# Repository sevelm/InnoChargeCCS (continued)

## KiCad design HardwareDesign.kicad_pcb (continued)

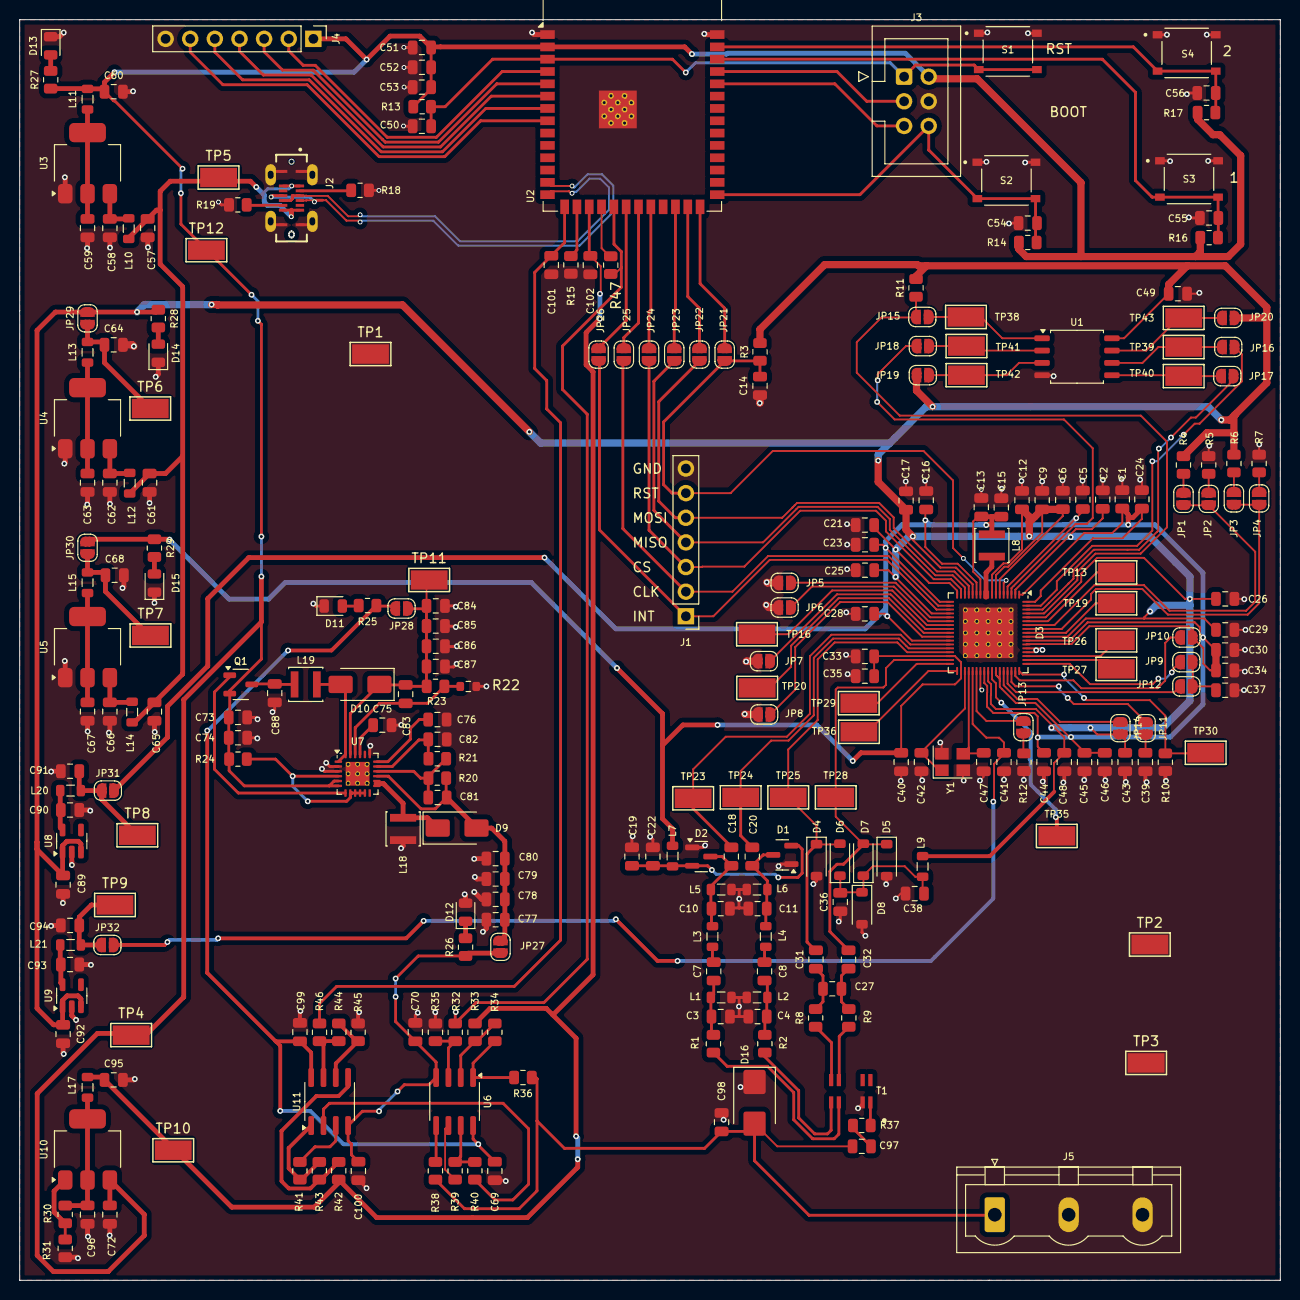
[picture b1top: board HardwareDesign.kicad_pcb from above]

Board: 2 copper layers, 130.0 x 130.0 mm, 271 parts (0 on the bottom side), 147 nets.

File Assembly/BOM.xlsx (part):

Designator | Value | Footprint | JLCPCB Part No# | Qty
L9 | GZ2012D601TF | Inductor_SMD:L_0805_2012Metric | C1017 | 1
L10 | GZ2012D601TF | Inductor_SMD:L_0805_2012Metric | C1017 | 1
L11 | GZ2012D601TF | Inductor_SMD:L_0805_2012Metric | C1017 | 1
L12 | GZ2012D601TF | Inductor_SMD:L_0805_2012Metric | C1017 | 1
L13 | GZ2012D601TF | Inductor_SMD:L_0805_2012Metric | C1017 | 1
L14 | GZ2012D601TF | Inductor_SMD:L_0805_2012Metric | C1017 | 1
L15 | GZ2012D601TF | Inductor_SMD:L_0805_2012Metric | C1017 | 1
L17 | GZ2012D601TF | Inductor_SMD:L_0805_2012Metric | C1017 | 1
L20 | GZ2012D601TF | Inductor_SMD:L_0805_2012Metric | C1017 | 1
L21 | GZ2012D601TF | Inductor_SMD:L_0805_2012Metric | C1017 | 1
C75 | 10nF | Capacitor_SMD:C_0805_2012Metric | C1710 | 1
C76 | 4.7nF | Capacitor_SMD:C_0805_2012Metric | C1744 | 1
C77 | 4.7uF | Capacitor_SMD:C_0805_2012Metric | C1779 | 1
C78 | 4.7uF | Capacitor_SMD:C_0805_2012Metric | C1779 | 1
C79 | 4.7uF | Capacitor_SMD:C_0805_2012Metric | C1779 | 1
C80 | 4.7uF | Capacitor_SMD:C_0805_2012Metric | C1779 | 1
C84 | 4.7uF | Capacitor_SMD:C_0805_2012Metric | C1779 | 1
C85 | 4.7uF | Capacitor_SMD:C_0805_2012Metric | C1779 | 1
C86 | 4.7uF | Capacitor_SMD:C_0805_2012Metric | C1779 | 1
C87 | 4.7uF | Capacitor_SMD:C_0805_2012Metric | C1779 | 1
C88 | 4.7uF | Capacitor_SMD:C_0805_2012Metric | C1779 | 1
C42 | 12pF | Capacitor_SMD:C_0805_2012Metric | C1792 | 1
C47 | 12pF | Capacitor_SMD:C_0805_2012Metric | C1792 | 1
C98 | 330pF | Capacitor_SMD:C_0805_2012Metric | C1815 | 1
C83 | 6.8pF | Capacitor_SMD:C_0805_2012Metric | C1832 | 1
D11 | LED | LED_SMD:LED_0805_2012Metric | C2297 | 1
D12 | LED | LED_SMD:LED_0805_2012Metric | C2297 | 1
D13 | LED | LED_SMD:LED_0805_2012Metric | C2297 | 1
D14 | LED | LED_SMD:LED_0805_2012Metric | C2297 | 1
D15 | LED | LED_SMD:LED_0805_2012Metric | C2297 | 1
C82 | 220nF | Capacitor_SMD:C_0805_2012Metric | C5378 | 1
U3 | AMS1117-3.3 | Package_TO_SOT_SMD:SOT-223-3_TabPin2 | C6186 | 1
U4 | AMS1117-3.3 | Package_TO_SOT_SMD:SOT-223-3_TabPin2 | C6186 | 1
U5 | AMS1117-3.3 | Package_TO_SOT_SMD:SOT-223-3_TabPin2 | C6186 | 1
D4 | B5819W SL | Diode_SMD:D_SOD-123 | C8598 | 1
D5 | B5819W SL | Diode_SMD:D_SOD-123 | C8598 | 1
D6 | B5819W SL | Diode_SMD:D_SOD-123 | C8598 | 1
D7 | B5819W SL | Diode_SMD:D_SOD-123 | C8598 | 1
Y1 | 25MHz X322525MOB4SI | Crystal:Crystal_SMD_3225-4Pin_3.2x2.5mm | C9006 | 1
C52 | 47uF | Capacitor_SMD:C_0805_2012Metric | C16780 | 1
C53 | 47uF | Capacitor_SMD:C_0805_2012Metric | C16780 | 1
C57 | 47uF | Capacitor_SMD:C_0805_2012Metric | C16780 | 1
C58 | 47uF | Capacitor_SMD:C_0805_2012Metric | C16780 | 1
C59 | 47uF | Capacitor_SMD:C_0805_2012Metric | C16780 | 1
C60 | 47uF | Capacitor_SMD:C_0805_2012Metric | C16780 | 1
C61 | 47uF | Capacitor_SMD:C_0805_2012Metric | C16780 | 1
C62 | 47uF | Capacitor_SMD:C_0805_2012Metric | C16780 | 1
C63 | 47uF | Capacitor_SMD:C_0805_2012Metric | C16780 | 1
C64 | 47uF | Capacitor_SMD:C_0805_2012Metric | C16780 | 1
C65 | 47uF | Capacitor_SMD:C_0805_2012Metric | C16780 | 1
C66 | 47uF | Capacitor_SMD:C_0805_2012Metric | C16780 | 1
C67 | 47uF | Capacitor_SMD:C_0805_2012Metric | C16780 | 1
C68 | 47uF | Capacitor_SMD:C_0805_2012Metric | C16780 | 1
C95 | 47uF | Capacitor_SMD:C_0805_2012Metric | C16780 | 1
R8 | 100Ω | Resistor_SMD:R_0805_2012Metric | C17408 | 1
R9 | 100Ω | Resistor_SMD:R_0805_2012Metric | C17408 | 1
R24 | 100Ω | Resistor_SMD:R_0805_2012Metric | C17408 | 1
R21 | 105KΩ | Resistor_SMD:R_0805_2012Metric | C17410 | 1
R3 | 10KΩ | Resistor_SMD:R_0805_2012Metric | C17414 | 1
R11 | 10KΩ | Resistor_SMD:R_0805_2012Metric | C17414 | 1
R13 | 10KΩ | Resistor_SMD:R_0805_2012Metric | C17414 | 1
R14 | 10KΩ | Resistor_SMD:R_0805_2012Metric | C17414 | 1
R15 | 10K | Resistor_SMD:R_0805_2012Metric | C17414 | 1
R16 | 10KΩ | Resistor_SMD:R_0805_2012Metric | C17414 | 1
R17 | 10KΩ | Resistor_SMD:R_0805_2012Metric | C17414 | 1
R40 | 10KΩ | Resistor_SMD:R_0805_2012Metric | C17414 | 1
R25 | 15KΩ | Resistor_SMD:R_0805_2012Metric | C17475 | 1
R26 | 15KΩ | Resistor_SMD:R_0805_2012Metric | C17475 | 1
R27 | 1KΩ | Resistor_SMD:R_0805_2012Metric | C17513 | 1
R28 | 1KΩ | Resistor_SMD:R_0805_2012Metric | C17513 | 1
R29 | 1KΩ | Resistor_SMD:R_0805_2012Metric | C17513 | 1
R32 | 1KΩ | Resistor_SMD:R_0805_2012Metric | C17513 | 1
R33 | 1KΩ | Resistor_SMD:R_0805_2012Metric | C17513 | 1
R36 | 1KΩ | Resistor_SMD:R_0805_2012Metric | C17513 | 1
R38 | 1KΩ | Resistor_SMD:R_0805_2012Metric | C17513 | 1
R39 | 1KΩ | Resistor_SMD:R_0805_2012Metric | C17513 | 1
R41 | 1KΩ | Resistor_SMD:R_0805_2012Metric | C17513 | 1
R42 | 1KΩ | Resistor_SMD:R_0805_2012Metric | C17513 | 1
R43 | 1KΩ | Resistor_SMD:R_0805_2012Metric | C17513 | 1
R44 | 1KΩ | Resistor_SMD:R_0805_2012Metric | C17513 | 1
R45 | 1KΩ | Resistor_SMD:R_0805_2012Metric | C17513 | 1
R47 | 1KΩ | Resistor_SMD:R_0805_2012Metric | C17513 | 1
R1 | 22Ω | Resistor_SMD:R_0805_2012Metric | C17561 | 1
R2 | 22Ω | Resistor_SMD:R_0805_2012Metric | C17561 | 1
R12 | 6.2KΩ | Resistor_SMD:R_0805_2012Metric | C17767 | 1
R34 | 7.5KΩ | Resistor_SMD:R_0805_2012Metric | C17807 | 1
R35 | 7.5KΩ | Resistor_SMD:R_0805_2012Metric | C17807 | 1
L8 | 4.7uH | Inductor_SMD:L_Sunlord_SWPA3015S | C19398 | 1
L18 | 4.7uH | Inductor_SMD:L_Sunlord_SWPA3015S | C19398 | 1
L19 | 4.7uH | Inductor_SMD:L_Sunlord_SWPA3015S | C19398 | 1
R37 | 180Ω | Resistor_SMD:R_0805_2012Metric | C25270 | 1
R4 | 3.3KΩ | Resistor_SMD:R_0805_2012Metric | C26010 | 1
R5 | 3.3KΩ | Resistor_SMD:R_0805_2012Metric | C26010 | 1
R6 | 3.3KΩ | Resistor_SMD:R_0805_2012Metric | C26010 | 1
R7 | 3.3KΩ | Resistor_SMD:R_0805_2012Metric | C26010 | 1
R18 | 5.1KΩ | Resistor_SMD:R_0805_2012Metric | C27834 | 1
R19 | 5.1KΩ | Resistor_SMD:R_0805_2012Metric | C27834 | 1
C1 | 100nF | Capacitor_SMD:C_0805_2012Metric | C28233 | 1
C2 | 100nF | Capacitor_SMD:C_0805_2012Metric | C28233 | 1
C5 | 100nF | Capacitor_SMD:C_0805_2012Metric | C28233 | 1
C6 | 100nF | Capacitor_SMD:C_0805_2012Metric | C28233 | 1
C12 | 100nF | Capacitor_SMD:C_0805_2012Metric | C28233 | 1
C14 | 100nF | Capacitor_SMD:C_0805_2012Metric | C28233 | 1
C15 | 100nF | Capacitor_SMD:C_0805_2012Metric | C28233 | 1
C16 | 100nF | Capacitor_SMD:C_0805_2012Metric | C28233 | 1
C17 | 100nF | Capacitor_SMD:C_0805_2012Metric | C28233 | 1
C21 | 100nF | Capacitor_SMD:C_0805_2012Metric | C28233 | 1
C23 | 100nF | Capacitor_SMD:C_0805_2012Metric | C28233 | 1
C24 | 100nF | Capacitor_SMD:C_0805_2012Metric | C28233 | 1
C25 | 100nF | Capacitor_SMD:C_0805_2012Metric | C28233 | 1
C26 | 100nF | Capacitor_SMD:C_0805_2012Metric | C28233 | 1
C28 | 100nF | Capacitor_SMD:C_0805_2012Metric | C28233 | 1
C29 | 100nF | Capacitor_SMD:C_0805_2012Metric | C28233 | 1
C30 | 100nF | Capacitor_SMD:C_0805_2012Metric | C28233 | 1
C31 | 100nF | Capacitor_SMD:C_0805_2012Metric | C28233 | 1
C32 | 100nF | Capacitor_SMD:C_0805_2012Metric | C28233 | 1
C34 | 100nF | Capacitor_SMD:C_0805_2012Metric | C28233 | 1
C35 | 100nF | Capacitor_SMD:C_0805_2012Metric | C28233 | 1
C36 | 100nF | Capacitor_SMD:C_0805_2012Metric | C28233 | 1
C37 | 100nF | Capacitor_SMD:C_0805_2012Metric | C28233 | 1
C38 | 100nF | Capacitor_SMD:C_0805_2012Metric | C28233 | 1
C39 | 100nF | Capacitor_SMD:C_0805_2012Metric | C28233 | 1
C40 | 100nF | Capacitor_SMD:C_0805_2012Metric | C28233 | 1
C41 | 100nF | Capacitor_SMD:C_0805_2012Metric | C28233 | 1
C43 | 100nF | Capacitor_SMD:C_0805_2012Metric | C28233 | 1
C44 | 100nF | Capacitor_SMD:C_0805_2012Metric | C28233 | 1
C45 | 100nF | Capacitor_SMD:C_0805_2012Metric | C28233 | 1
C46 | 100nF | Capacitor_SMD:C_0805_2012Metric | C28233 | 1
C48 | 100nF | Capacitor_SMD:C_0805_2012Metric | C28233 | 1
C49 | 100nF | Capacitor_SMD:C_0805_2012Metric | C28233 | 1
C50 | 100nF | Capacitor_SMD:C_0805_2012Metric | C28233 | 1
C51 | 100nF | Capacitor_SMD:C_0805_2012Metric | C28233 | 1
C54 | 100nF | Capacitor_SMD:C_0805_2012Metric | C28233 | 1
C55 | 100nF | Capacitor_SMD:C_0805_2012Metric | C28233 | 1
C56 | 100nF | Capacitor_SMD:C_0805_2012Metric | C28233 | 1
C69 | 100nF | Capacitor_SMD:C_0805_2012Metric | C28233 | 1
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
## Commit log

2024-05-23 Project Skeleton
2024-06-03 Added References
2024-06-09 Initial Draft of Test Board
2024-06-09 1st test board manufacturing files
2024-06-11 Drill files added in gerber
